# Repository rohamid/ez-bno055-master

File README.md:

## BNO055
BNO055 sensor breakout board with Adafruit's Stemma QT style connector. All pin and I2C connector is similar to the Adafruit's BNO055 breakout board to ensure the compatibility.

### BNO055 Top

### BNO055 Bottom

### BNO055 PCB dimension

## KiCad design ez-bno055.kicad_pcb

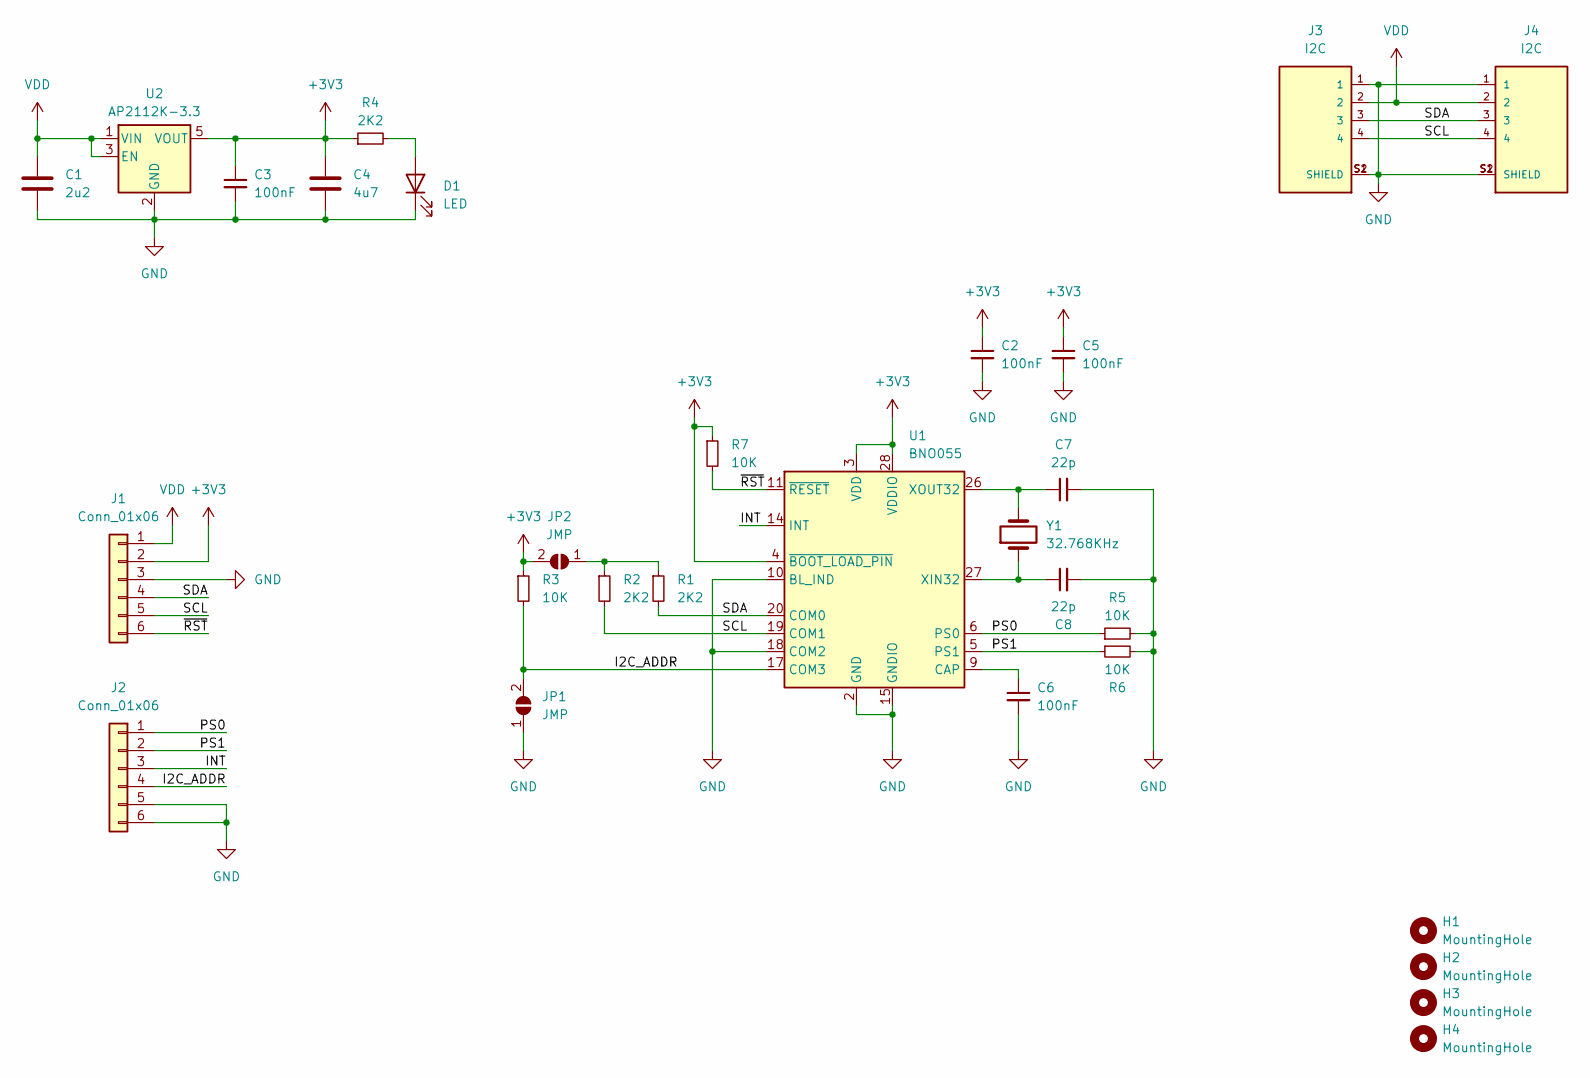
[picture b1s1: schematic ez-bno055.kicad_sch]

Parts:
C1: 2u2; C_0603_1608Metric
C2, C3, C5, C6: 100nF; C_0402_1005Metric
C4: 4u7; C_0603_1608Metric
C7, C8: 22p; C_0402_1005Metric
D1: LED; LED_0805_2012Metric
H1, H2, H3, H4: MountingHole; MountingHole_3.2mm_M3
J1, J2: Conn_01x06; PinHeader_1x06_P2.54mm_Vertical
J3, J4: I2C; JST_SM04B-SRSS-TB_LF__SN_
JP1, JP2: JMP; SolderJumper-2_P1.3mm_Open_RoundedPad1.0x1.5mm
R1, R2, R4: 2K2; R_0402_1005Metric
R3, R5, R6, R7: 10K; R_0402_1005Metric
U1: BNO055; LGA-28_5.2x3.8mm_P0.5mm
U2: AP2112K-3.3; SOT-23-5
Y1: 32.768KHz; Crystal_SMD_3215-2Pin_3.2x1.5mm

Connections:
+3V3: C2.1, C3.1, C4.1, C5.1, J1.2, JP2.2 (B), R3.1, R4.1, R7.1, U1.3 (VDD), U1.4 (~BOOT_LOAD_PIN), U1.28 (VDDIO), U2.5 (VOUT)
/I2C_ADDR: J2.4, JP1.2 (B), R3.2, U1.17 (COM3)
/INT: J2.3, U1.14 (INT)
/PS0: J2.1, R5.1, U1.6 (PS0)
/PS1: J2.2, R6.1, U1.5 (PS1)
/SCL: J1.5, J3.4, J4.4, R2.2, U1.19 (COM1)
/SDA: J1.4, J3.3, J4.3, R1.2, U1.20 (COM0)
/~RST: J1.6, R7.2, U1.11 (~RESET)
GND: C1.2, C2.2, C3.2, C4.2, C5.2, C6.2, C7.2, C8.2, D1.1 (K), J1.3, J2.5, J2.6, J3.1, J3.S1 (SHIELD), J3.S2 (SHIELD), J4.1, J4.S1 (SHIELD), J4.S2 (SHIELD), JP1.1 (A), R5.2, R6.2, U1.2 (GND), U1.10 (BL_IND), U1.15 (GNDIO), U1.16 (GNDIO), U1.18 (COM2), U1.25 (GNDIO), U2.2 (GND)
unnamed: D1.2 (A), R4.2
unnamed: JP2.1 (A), R1.1, R2.1
unnamed: C6.1, U1.9 (CAP)
unnamed: C8.1, U1.27 (XIN32), Y1.1
unnamed: C7.1, U1.26 (XOUT32), Y1.2
VDD: C1.1, J1.1, J3.2, J4.2, U2.1 (VIN), U2.3 (EN)

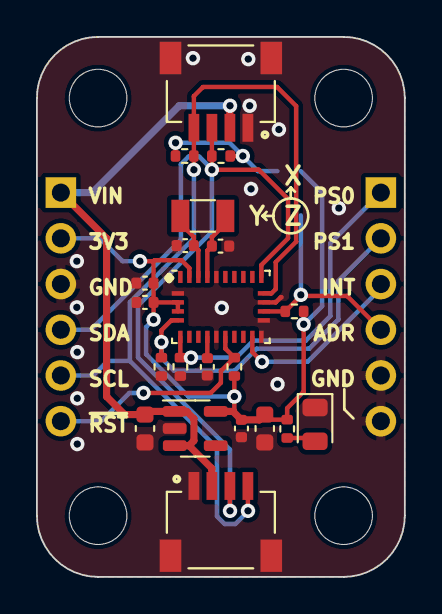
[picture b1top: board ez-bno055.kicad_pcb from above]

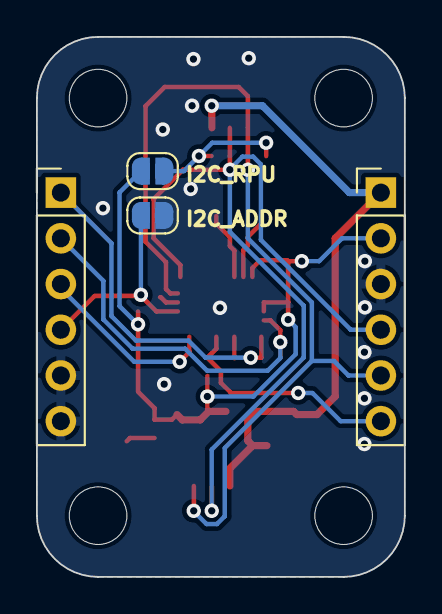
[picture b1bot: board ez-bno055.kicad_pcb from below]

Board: 2 copper layers, 20.4 x 30.0 mm, 29 parts (4 on the bottom side), 15 nets.

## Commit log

2024-02-11 Initial init, finished tracks and vias
2024-02-11 add README
2024-02-11 add image
2024-02-11 add image to the README
2024-02-11 add image to the README (2nd try)
2024-02-11 add image to the README (3rd try)
2024-02-12 Changes crystal to 3215 size
